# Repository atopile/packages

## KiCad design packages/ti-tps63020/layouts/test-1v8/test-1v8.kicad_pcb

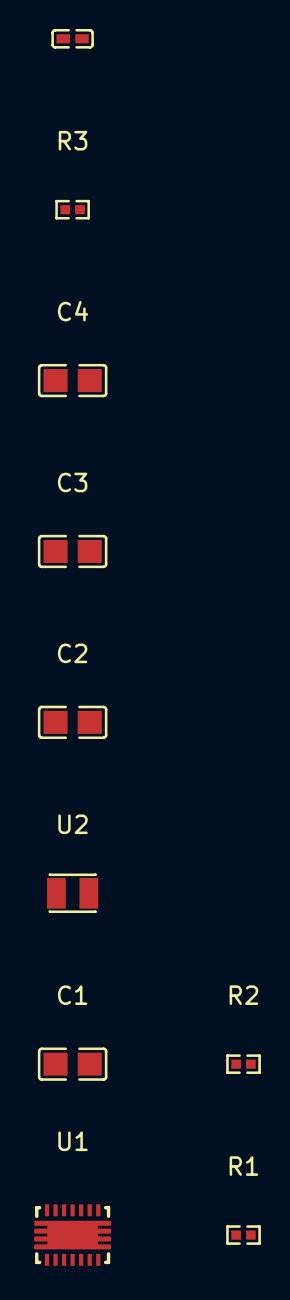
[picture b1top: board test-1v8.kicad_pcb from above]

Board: 2 copper layers, 10 parts (0 on the bottom side), 8 nets, no tracks yet.

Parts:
C1, C2, C3, C4: 10µF ±10% 25V X5R; C0805
C5: 100nF ±10% 16V X7R; C0402
R1: 3.9kΩ ±1% 62.5mW; R0402
R2: 10kΩ ±1% 62.5mW; R0402
R3: 1MΩ ±1% 62.5mW; R0402
U1: VSON-14_L4.0-W3.0-P0.50-BL-EP_TI_DSJ
U2: IND-SMD_L2.5-W2.0_WPN252012H

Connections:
EN: C5.1, U1.1, U1.12
FB: R1.1, R2.2, U1.3
L1: U1.8, U1.9, U2.1
L2: U1.6, U1.7, U2.2
PG: R3.1, U1.14
VIN: C1.1, C2.1, U1.10, U1.11
gnd: C1.2, C2.2, C3.2, C4.2, C5.2, R1.2, R3.2, U1.2, U1.13, U1.15
hv: C3.1, C4.1, R2.1, U1.4, U1.5

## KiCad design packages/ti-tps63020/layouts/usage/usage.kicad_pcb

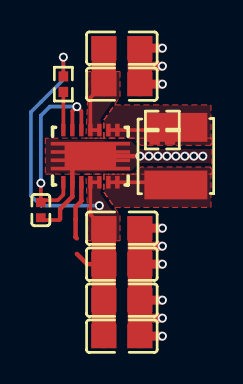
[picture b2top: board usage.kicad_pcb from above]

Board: 2 copper layers, 12 parts (0 on the bottom side), 9 nets.

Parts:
C1, C2: 10µF ±10%; C0805
C3, C4, C5, C6: 22µF ±20%; C0805
C7: 100nF ±10%; C0402
L1: L 1µH ±20%; IND-SMD_L4.0-W4.0
R1: 107kΩ ±1%; R0402
R2: 19.1kΩ ±1%; R0402
R3: 1MΩ ±1%; R0402
U1: VSON-14_L4.0-W3.0-P0.50-BL-EP_TI_DSJ

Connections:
6: L1.2, U1.6, U1.7
8: L1.1, U1.8, U1.9
PG: R3.1, U1.14
hv: C7.1, U1.1, U1.12, U1.13
input_decoupling_capacitor[1]-power-hv: C1.1, C2.1, U1.10, U1.11
input_decoupling_capacitor[1]-power-lv: C1.2, C2.2, U1.2, U1.15
output_decoupling_capacitor[3]-power-hv: C3.1, C4.1, C5.1, C6.1, R1.1, R3.2, U1.4, U1.5
output_decoupling_capacitor[3]-power-lv: C3.2, C4.2, C5.2, C6.2, R2.2
ref_out-hv: R1.2, R2.1, U1.3

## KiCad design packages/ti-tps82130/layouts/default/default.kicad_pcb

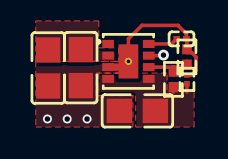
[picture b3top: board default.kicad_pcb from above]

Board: 2 copper layers, 8 parts (0 on the bottom side), 6 nets.

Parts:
C1, C4: 4.7µF ±10%; C0805
C2: 47µF ±20%; C0805
C3: 1nF ±10%; C0201
R1: 100kΩ ±1%; R0201
R2: 3.74kΩ ±1%; R0402
R3: 4.02kΩ ±1%; R0402
U1: USIP-8_L3.0-W2.8-P0.65-TL-EP

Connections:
hv: R2.2, R3.1, U1.6
input_power_decoupling_capacitors[1]-power-hv: C1.1, C4.1, U1.2
lv: C2.2, R1.2, R3.2
output_power_decoupling_capacitor-power-hv: C2.1, R1.1, R2.1, U1.4, U1.5
soft_start_capacitor-power-hv: C3.1, U1.8
soft_start_capacitor-power-lv: C1.2, C3.2, C4.2, U1.3, U1.9

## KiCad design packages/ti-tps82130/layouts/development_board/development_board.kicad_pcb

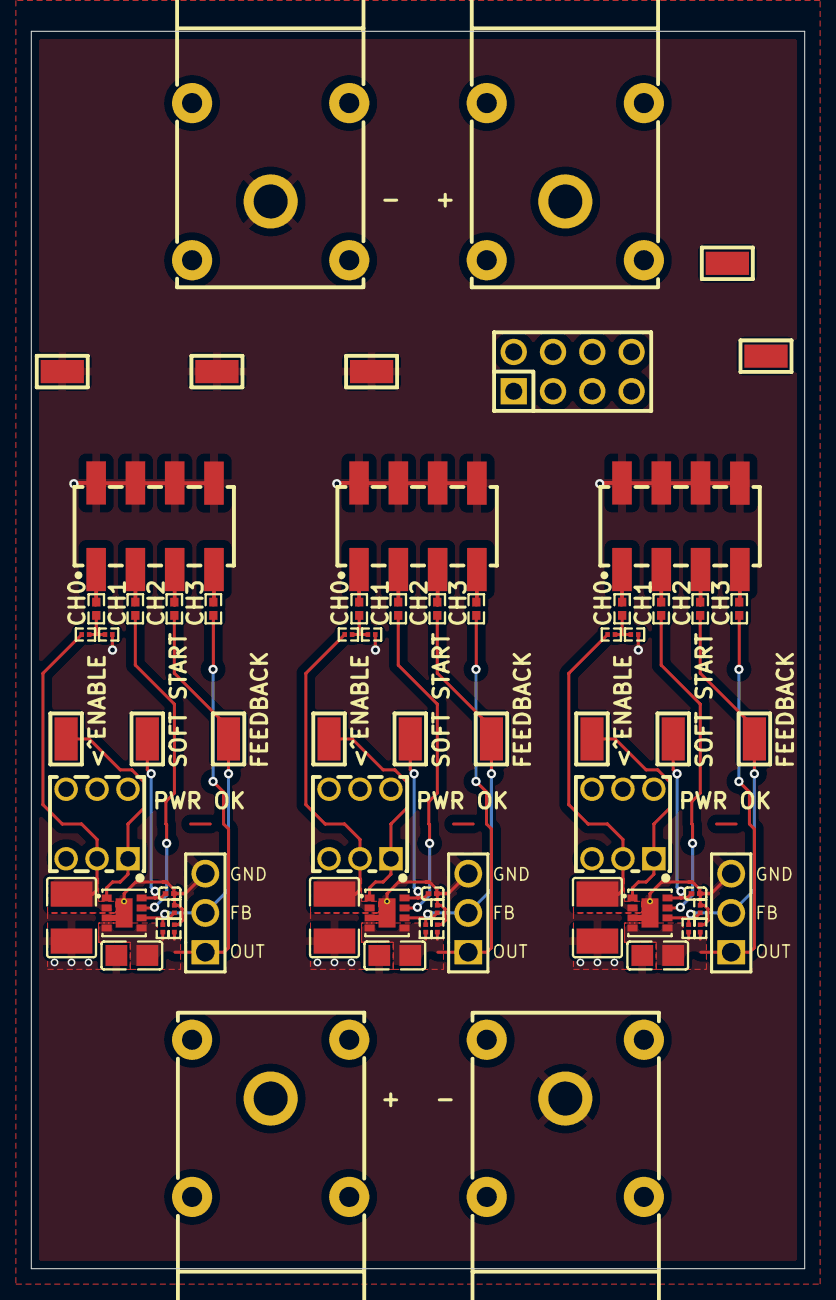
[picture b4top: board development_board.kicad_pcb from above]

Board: 2 copper layers, 50.0 x 80.0 mm, 67 parts (0 on the bottom side), 33 nets.

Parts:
C1, C4, C7: 22µF ±10% 25V X7R; C1210
C2, C5, C8: 47µF ±20% 10V X5R; C0805
C3, C6, C9: 3.3nF ±10% 50V X7R; C0201
CN3, CN4, CN5, CN11, CN14: SMD_RH-5015
CN9, CN12: ANT-TH_L33.0-W12.0_BLACK
CN10, CN13: ANT-TH_L33.0-W12.0_RED
H1: HDR-TH_8P-P2.54-V-M-R2-C4-S2.54
H2, H3, H4: HDR-TH_3P-P2.54-V-M-1
HDR1, HDR2, HDR3: HDR-SMD_8P-P2.54-V-M-R2-C4-LS7.4
R1, R2, R10, R11, R19, R20: 100kΩ ±1% 50mW; R0201
R3: 249kΩ ±1% 50mW; R0201
R4: 3.3kΩ ±1% 50mW; R0201
R5: 10kΩ ±1% 50mW; R0201
R6, R7, R8, R9, R15, R16, R17, R18, R24, R25, R26, R27: 1kΩ ±1% 62.5mW; R0402
R12: 390kΩ ±1% 50mW; R0201
R13, R22: 1kΩ ±1% 50mW; R0201
R14: 5.1kΩ ±1% 50mW; R0201
R21: 75kΩ ±1% 50mW; R0201
R23: 240Ω ±1% 50mW; R0201
SW1, SW2, SW3: SW-TH_5.8ZSGT
U1, U2, U4, U5, U6, U8, U9, U10, U12: SMD_RH-5015
U3, U7, U11: USIP-8_L3.0-W2.8-P0.65-TL-EP

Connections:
-hv-0: C1.1, C4.1, C7.1, CN10.5, CN11.1, H1.7, R2.1, R11.1, R20.1, SW1.2, SW2.2, SW3.2, U3.2, U7.2, U11.2
-hv-1: C2.1, H1.3, H2.1, R3.1, R5.1, R9.1, U3.4, U3.5
-hv-2: C5.1, H1.5, H3.1, R12.1, R14.1, R18.1, U7.4, U7.5
-pins[1]: CN13.5, CN14.1, H1.2, H1.4, H1.6, H1.8
gnd: C1.2, C2.2, C3.2, C4.2, C5.2, C6.2, C7.2, C8.2, C9.2, CN3.1, CN4.1, CN5.1, CN9.5, CN12.5, H2.3, H3.3, H4.3, HDR1.2, HDR1.4, HDR1.6, HDR1.8, HDR2.2, HDR2.4, HDR2.6, HDR2.8, HDR3.2, HDR3.4, HDR3.6, HDR3.8, R1.2, R3.2, R4.2, R10.2, R12.2, R13.2, R19.2, R21.2, R22.2, U3.3, U3.9, U7.3, U7.9, U11.3, U11.9
pins[0]: C8.1, H1.1, H4.1, R21.1, R23.1, R27.1, U11.4, U11.5
regulator_3v3-PG: R7.1, U3.7
regulator_3v3-SS_TR: C3.1, U3.8, U4.1
regulator_3v3-line: R1.1, R2.2, R6.1
regulator_3v3-output[0]: SW1.1, U1.1, U3.1
regulator_3v3-pins[1]: H2.2, R4.1, R5.2, R8.1, U2.1, U3.6
regulator_3v3.scope_header-_1: HDR1.1, R6.2
regulator_3v3.scope_header-_3: HDR1.3, R7.2
regulator_3v3.scope_header-_5: HDR1.5, R8.2
regulator_3v3.scope_header-_7: HDR1.7, R9.2
regulator_5v-PG: R16.1, U7.7
regulator_5v-SS_TR: C6.1, U7.8, U8.1
regulator_5v-line: R10.1, R11.2, R15.1
regulator_5v-output[0]: SW2.1, U5.1, U7.1
regulator_5v-pins[1]: H3.2, R13.1, R14.2, R17.1, U6.1, U7.6
regulator_5v.scope_header-_1: HDR2.1, R15.2
regulator_5v.scope_header-_3: HDR2.3, R16.2
regulator_5v.scope_header-_5: HDR2.5, R17.2
regulator_5v.scope_header-_7: HDR2.7, R18.2
regulator_adj-PG: R25.1, U11.7
regulator_adj-SS_TR: C9.1, U11.8, U12.1
regulator_adj-line: R19.1, R20.2, R24.1
regulator_adj-output[0]: SW3.1, U9.1, U11.1
regulator_adj-pins[1]: H4.2, R22.1, R23.2, R26.1, U10.1, U11.6
regulator_adj.scope_header-_1: HDR3.1, R24.2
regulator_adj.scope_header-_3: HDR3.3, R25.2
regulator_adj.scope_header-_5: HDR3.5, R26.2
regulator_adj.scope_header-_7: HDR3.7, R27.2

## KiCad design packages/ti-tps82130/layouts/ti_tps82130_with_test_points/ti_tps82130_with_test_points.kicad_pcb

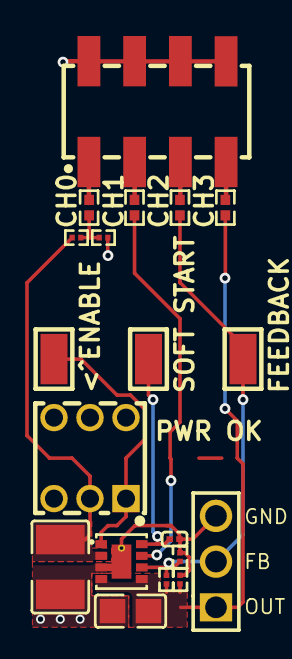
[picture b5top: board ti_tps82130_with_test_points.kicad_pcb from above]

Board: 2 copper layers, 19 parts (0 on the bottom side), 12 nets.

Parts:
C1: 22µF ±10% 25V X7R; C1210
C2: 47µF ±20% 10V X5R; C0805
C3: 1nF ±10% 50V X7R; C0201
CN1, CN2, CN3: SMD_RH-5015
H1: HDR-TH_3P-P2.54-V-M-1
HDR1: HDR-SMD_8P-P2.54-V-M-R2-C4-LS7.4
R2, R5, R6: 100kΩ ±1% 50mW; R0201
R3: 4.7kΩ ±1% 50mW; R0201
R4: 10kΩ ±1% 50mW; R0201
R7, R8, R9, R10: 1kΩ ±1% 62.5mW; R0402
SW1: SW-TH_5.8ZSGT
U1: USIP-8_L3.0-W2.8-P0.65-TL-EP

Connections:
PG: R8.1, U1.7
SS_TR: C3.1, CN3.1, U1.8
_1: HDR1.1, R7.2
_3: HDR1.3, R8.2
_5: HDR1.5, R9.2
_7: HDR1.7, R10.2
gnd: C1.2, C2.2, C3.2, H1.3, HDR1.2, HDR1.4, HDR1.6, HDR1.8, R2.2, R3.2, R5.2, U1.3, U1.9
input[0]: C1.1, R6.1, SW1.2, U1.2
line: R5.1, R6.2, R7.1
output[0]: CN1.1, SW1.1, U1.1
pins[0]: C2.1, H1.1, R2.1, R4.1, R10.1, U1.4, U1.5
pins[1]: CN2.1, H1.2, R3.1, R4.2, R9.1, U1.6
